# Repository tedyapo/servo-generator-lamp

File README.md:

# servo-generator-lamp
Hand crank flashlight using a modified RC servo as a generator

See [my hackaday.io project page](https://hackaday.io/project/36391-servo-generator-light) for full details.

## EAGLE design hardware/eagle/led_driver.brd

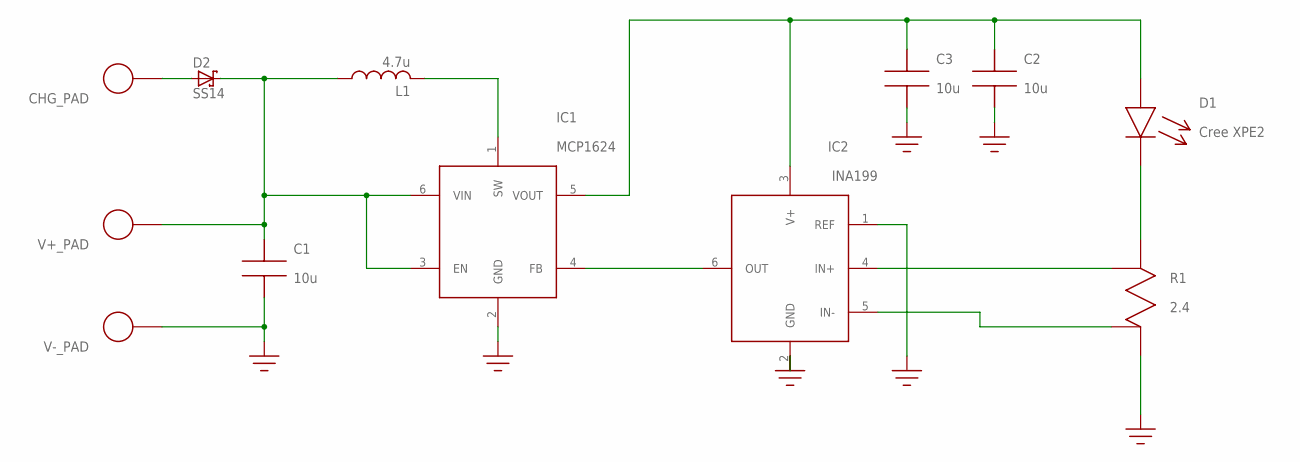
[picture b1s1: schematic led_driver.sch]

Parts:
C1, C2, C3: 10u; 1206
CHG_PAD: ICSP_PAD100MIL_SQUARE; 100MIL_PAD
D1: Cree XPE2; CREE_XPE_LED
D2: SS14
IC1: MCP1624; SOT23-6
IC2: INA199; SC70-6
L1: 4.7u; 4040_INDUCTOR
R1: 2.4; R0805_KELVIN
V+_PAD: ICSP_PAD100MIL_SQUARE; 100MIL_PAD
V-_PAD: ICSP_PAD100MIL_SQUARE; 100MIL_PAD

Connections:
GND: C1.P$2, C2.P$2, C3.P$2, IC1.2 (GND), IC2.1 (REF), IC2.2 (GND), R1.B1, V-_PAD.P$1
unnamed: C1.P$1, D2.C, IC1.3 (EN), IC1.6 (VIN), L1.P$1 (1), V+_PAD.P$1
unnamed: IC1.1 (SW), L1.P$2 (2)
unnamed: IC2.4 (IN+), R1.A2
unnamed: C2.P$1, C3.P$1, D1.A, IC1.5 (VOUT), IC2.3 (V+)
unnamed: IC1.4 (FB), IC2.6 (OUT)
unnamed: IC2.5 (IN-), R1.B2
unnamed: CHG_PAD.P$1, D2.A
unnamed: D1.C, R1.A1

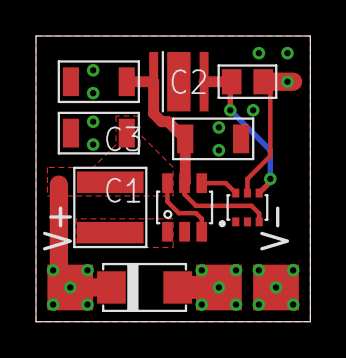
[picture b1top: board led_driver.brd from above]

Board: 2 copper layers, 15.2 x 15.9 mm, 12 parts (0 on the bottom side), 9 nets.

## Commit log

2018-02-02 first checkin
